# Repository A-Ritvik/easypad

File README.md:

# easypad
A repository for my custom macropad (easypad) containing a full 3d cad along with pcb, schematic, and code (used qmk firmware) files.
Features a rotary encoder, a 4*3 keyboard matrix , and a 0.91" OLED Display. Functionally, the rotary encoder can change volume; the keyboard matrix includes w/a/s/d/1/2/3/esc/enter/sleep/power on/shut down; and the display is currently set to display Capslock, numlock, scrollock, and the layout of the macropad.
# Full MacroPad 3d Model: 
Uses 4 M3 screws and heatset inserts to fit together. The case features a 15 degree tilt downwards, and is made of only 2 parts (the top and bottom all 3d printable)

Case:

# Schematic & PCB: 
They were created using kiCAD

# Bill of Materials:
(a full BOM.csv file can also be found under the production folder)
Here's everything you would need to build this: 
- 12x DSA Keycaps
- 12x Cherry_MX Switches
- 4x M3x16mm screws
- 4x M3x5mx4mm heatset inserts
- 1x EC11 Rotary Encoder
- 1x Seeed XIAO RP2040 Microporcessor
- 12x 1N4148 DO-35 Diodes
- 1x 0.91" 128x32 OLED Display
- 1x Case (2 3D Printed Parts)

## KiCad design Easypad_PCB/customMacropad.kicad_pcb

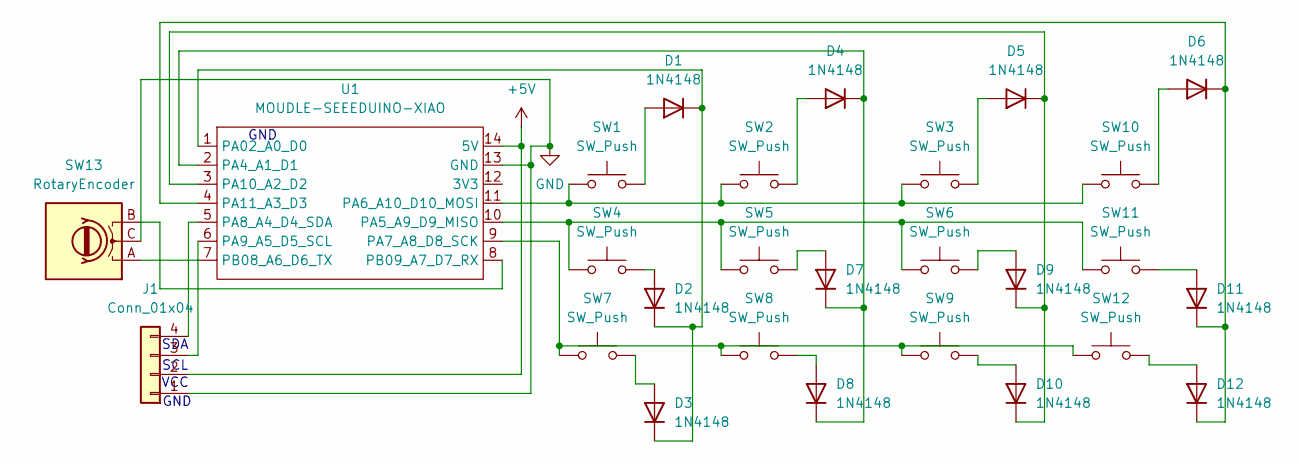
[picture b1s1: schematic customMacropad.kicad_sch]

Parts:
D1, D2, D3, D4, D5, D6, D7, D8, D9, D10, D11, D12: 1N4148; D_DO-35_SOD27_P7.62mm_Horizontal
J1: Conn_01x04; SSD1306-0.91-OLED-4pin-128x32 (1)
SW1, SW2, SW3, SW4, SW5, SW6, SW7, SW8, SW9, SW10, SW11, SW12: SW_Push; SW_Cherry_MX_1.00u_PCB
SW13: RotaryEncoder; RotaryEncoder_Alps_EC11E_Vertical_H20mm
U1: MOUDLE-SEEEDUINO-XIAO; XIAO-Generic-Hybrid-14P-2.54-21X17.8MM

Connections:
+5V: J1.2, U1.14 (5V)
GND: J1.1, SW13.C, U1.13 (GND)
unnamed: D1.2 (A), SW1.2
unnamed: D1.1 (K), D2.1 (K), D3.1 (K), U1.1 (PA02_A0_D0)
unnamed: D2.2 (A), SW4.2
unnamed: D3.2 (A), SW7.2
unnamed: D4.2 (A), SW2.2
unnamed: D4.1 (K), D7.1 (K), D8.1 (K), U1.2 (PA4_A1_D1)
unnamed: D5.2 (A), SW3.2
unnamed: D6.2 (A), SW10.2
unnamed: D7.2 (A), SW5.2
unnamed: D8.2 (A), SW8.2
unnamed: D9.2 (A), SW6.2
unnamed: D10.2 (A), SW9.2
unnamed: D5.1 (K), D9.1 (K), D10.1 (K), U1.3 (PA10_A2_D2)
unnamed: D11.2 (A), SW11.2
unnamed: D6.1 (K), D11.1 (K), D12.1 (K), U1.4 (PA11_A3_D3)
unnamed: D12.2 (A), SW12.2
unnamed: J1.3, U1.6 (PA9_A5_D5_SCL)
unnamed: J1.4, U1.5 (PA8_A4_D4_SDA)
unnamed: SW4.1, SW5.1, SW6.1, SW11.1, U1.10 (PA5_A9_D9_MISO)
unnamed: SW1.1, SW2.1, SW3.1, SW10.1, U1.11 (PA6_A10_D10_MOSI)
unnamed: SW7.1, SW8.1, SW9.1, SW12.1, U1.9 (PA7_A8_D8_SCK)
unnamed: SW13.A, U1.7 (PB08_A6_D6_TX)
unnamed: SW13.B, U1.8 (PB09_A7_D7_RX)

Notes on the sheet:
SCL
VCC
SDA
GND

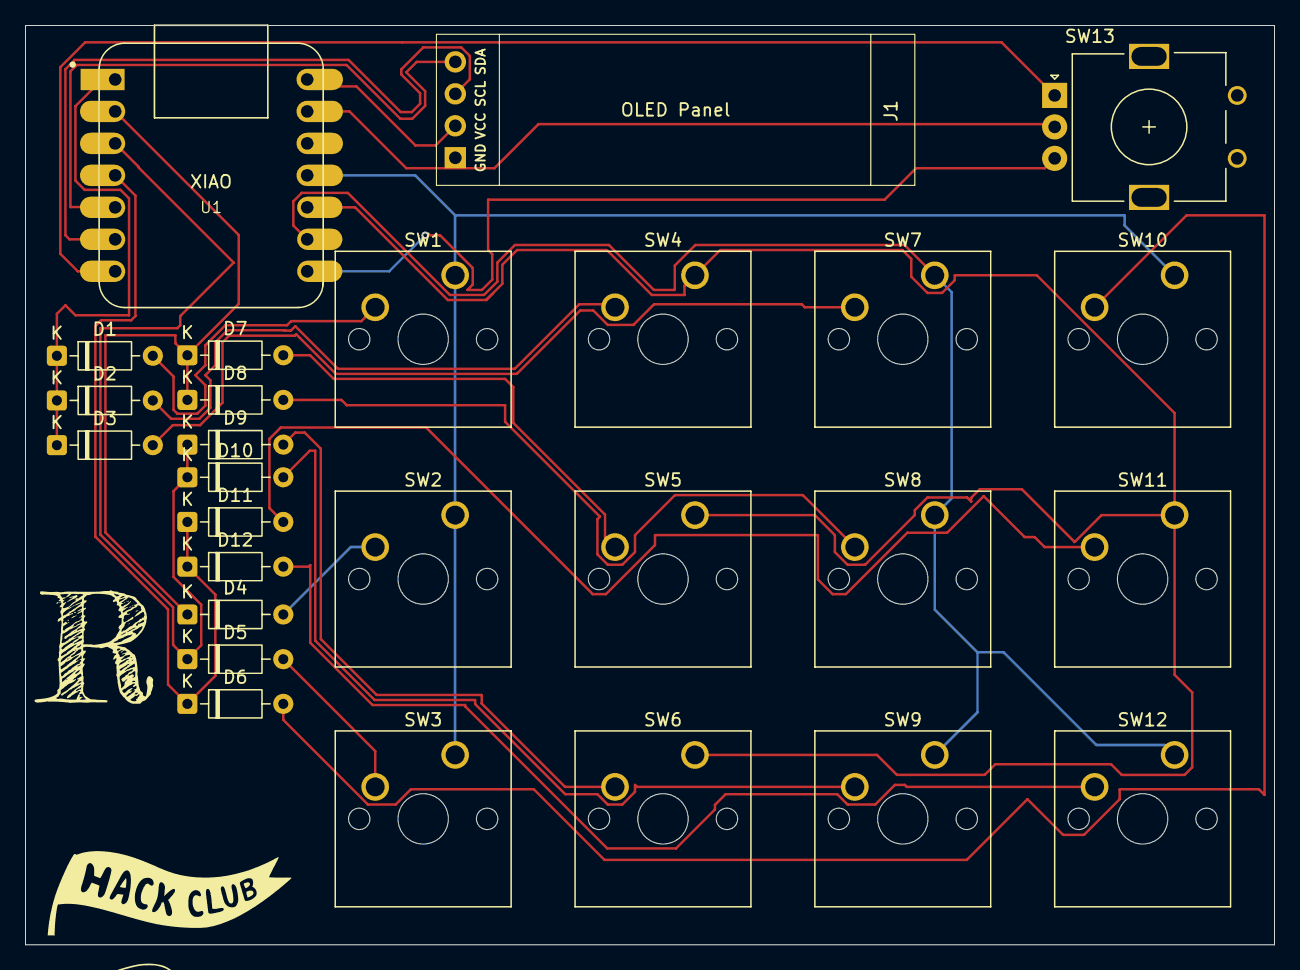
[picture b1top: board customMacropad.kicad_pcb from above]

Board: 2 copper layers, 99.2 x 73.0 mm, 27 parts (0 on the bottom side), 25 nets.

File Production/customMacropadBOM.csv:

"Id";"Designator";"Footprint";"Quantity";"Designation";"Supplier and ref";
1;"D1, D2, D3, D4, D5, D6, D7, D8, D9, D10, D11, D12";"D_DO-35_SOD27_P7.62mm_Horizontal";12;"1N4148";;;
2;"J1";"SSD1306-0.91-OLED-4pin-128x32 (1)";1;"Conn_01x04";;;
3;"SW1, SW2, SW3, SW4, SW5, SW6, SW7, SW8, SW9, SW10, SW11, SW12";"SW_Cherry_MX_1.00u_PCB";12;"SW_Push";;;
4;"SW13";"RotaryEncoder_Alps_EC11E_Vertical_H20mm";1;"RotaryEncoder";;;
5;"U1";"XIAO-Generic-Hybrid-14P-2.54-21X17.8MM";1;"MOUDLE-SEEEDUINO-XIAO";;;

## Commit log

2026-06-19 Added CAD files
2026-06-19 Added PCB Files for the Easypad
2026-06-19 Create
2026-06-19 Added Firmware for the Easypad
2026-06-19 Update README.md
    Added feature details for rotary encoder, keyboard matrix, and OLED display.
2026-06-19 Update README.md
    Expanded feature list and added images for 3D model, schematic, PCB, and case.
2026-06-19 Update README.md
    Added detailed descriptions for the case, schematic, PCB, and bill of materials for the easypad project.
2026-06-27 Update README with BOM.csv file location
    Added a note about the availability of the BOM.csv file in the production folder.
